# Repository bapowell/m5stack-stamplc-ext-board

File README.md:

# m5stack-stamplc-ext-board

KiCad PCB design for utilizing the GPIO.EXT port on an [M5Stack M5Stamp PLC](https://shop.m5stack.com/products/m5stamp-plc-controller-with-m5stamps3)

It's a protoboard-type PCB that includes:
* 3.3V regulator
* Voltage and ground rails
* SPI breakouts
* I2C breakouts
* Areas for ad-hoc components

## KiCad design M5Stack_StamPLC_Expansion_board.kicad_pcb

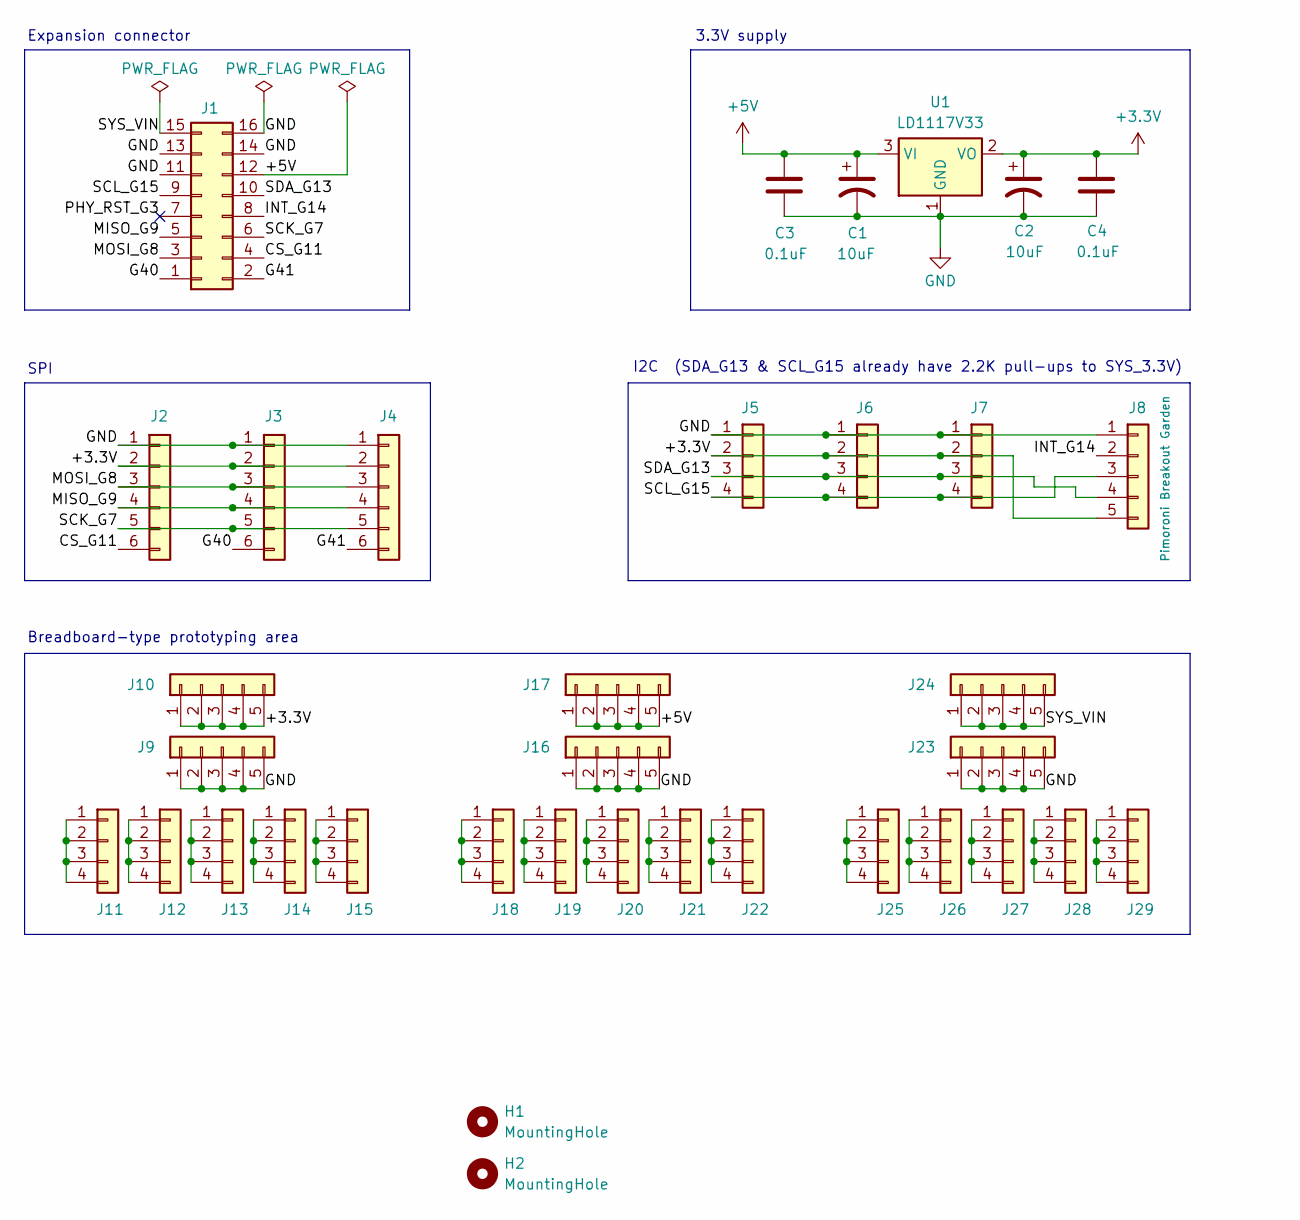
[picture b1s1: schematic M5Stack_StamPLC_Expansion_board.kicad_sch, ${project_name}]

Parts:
C1, C2: 10uF; CP_Radial_D6.3mm_P2.50mm
C3, C4: 0.1uF; C_Disc_D5.0mm_W2.5mm_P5.00mm
H1, H2: MountingHole; MountingHole_2mm
J1: Conn_02x08_Odd_Even; PinHeader_2x08_P2.54mm_Horizontal
J2, J3, J4: Conn_01x06; PinSocket_1x06_P2.54mm_Vertical
J5, J6, J7: Conn_01x04; PinSocket_1x04_P2.54mm_Vertical
J8: Conn_01x05; PinSocket_1x05_P2.54mm_Vertical
J9, J10, J16, J17, J23, J24: Conn_01x05; PinSocket_1x05_P2.54mm_Vertical_for_breadboard
J11, J12, J13, J14, J15, J18, J19, J20, J21, J22, J25, J26, J27, J28, J29: Conn_01x04; PinSocket_1x04_P2.54mm_Vertical_for_breadboard
U1: LD1117V33; TO-220-3_Vertical

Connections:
+3.3V: C2.1, C4.1, J2.2, J3.2, J4.2, J5.2, J6.2, J7.2, J8.5, J10.1, J10.2, J10.3, J10.4, J10.5, U1.2 (VO)
+5V: C1.1, C3.1, J1.12, J17.1, J17.2, J17.3, J17.4, J17.5, U1.3 (VI)
/CS_G11: J1.4, J2.6
/G40: J1.1, J3.6
/G41: J1.2, J4.6
/INT_G14: J1.8, J8.2
/MISO_G9: J1.5, J2.4, J3.4, J4.4
/MOSI_G8: J1.3, J2.3, J3.3, J4.3
/PHY_RST_G3: J1.7
/SCK_G7: J1.6, J2.5, J3.5, J4.5
/SCL_G15: J1.9, J5.4, J6.4, J7.4, J8.3
/SDA_G13: J1.10, J5.3, J6.3, J7.3, J8.4
/SYS_VIN: J1.15, J24.1, J24.2, J24.3, J24.4, J24.5
GND: C1.2, C2.2, C3.2, C4.2, J1.11, J1.13, J1.14, J1.16, J2.1, J3.1, J4.1, J5.1, J6.1, J7.1, J8.1, J9.1, J9.2, J9.3, J9.4, J9.5, J16.1, J16.2, J16.3, J16.4, J16.5, J23.1, J23.2, J23.3, J23.4, J23.5, U1.1 (GND)
unnamed: J11.1, J11.2, J11.3, J11.4
unnamed: J12.1, J12.2, J12.3, J12.4
unnamed: J13.1, J13.2, J13.3, J13.4
unnamed: J14.1, J14.2, J14.3, J14.4
unnamed: J15.1, J15.2, J15.3, J15.4
unnamed: J18.1, J18.2, J18.3, J18.4
unnamed: J19.1, J19.2, J19.3, J19.4
unnamed: J20.1, J20.2, J20.3, J20.4
unnamed: J21.1, J21.2, J21.3, J21.4
unnamed: J22.1, J22.2, J22.3, J22.4
unnamed: J25.1, J25.2, J25.3, J25.4
unnamed: J26.1, J26.2, J26.3, J26.4
unnamed: J27.1, J27.2, J27.3, J27.4
unnamed: J28.1, J28.2, J28.3, J28.4
unnamed: J29.1, J29.2, J29.3, J29.4

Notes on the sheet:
Breadboard-type prototyping area
3.3V supply
Expansion connector
I2C (SDA_G13 & SCL_G15 already have 2.2K pull-ups to SYS_3.3V)
SPI

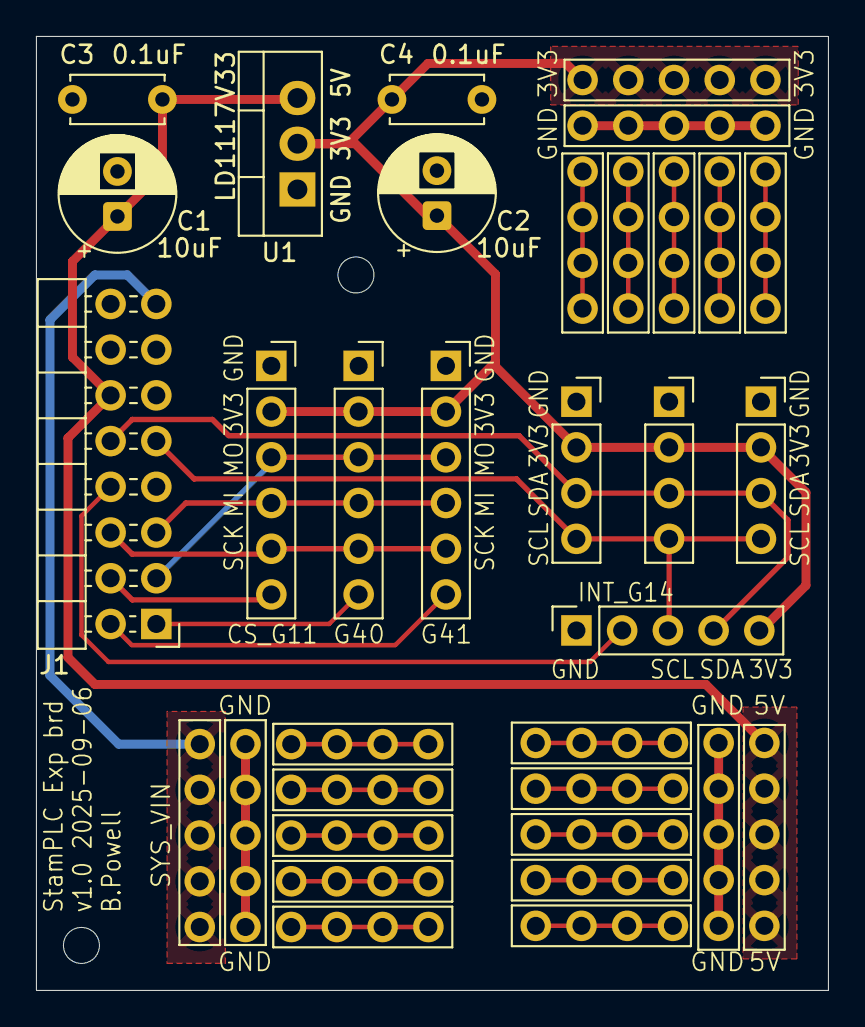
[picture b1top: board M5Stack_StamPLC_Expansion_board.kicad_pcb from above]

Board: 2 copper layers, 44.0 x 53.0 mm, 36 parts (0 on the bottom side), 28 nets.

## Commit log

2025-10-02 Added files
2025-10-02 Fixed images in README.md
